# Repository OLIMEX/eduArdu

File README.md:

# eduArdu
Open Source Hardware Educational board based on Arduino Leonardo

Product page: https://www.olimex.com/Products/Duino/AVR/eduArdu/open-source-hardware

Introduction video: https://youtu.be/3kFrveMF56s

# Getting started

## Arduino IDE

* [Download and install Arduino IDE](https://www.arduino.cc/en/Main/Software)
* Open Arduino IDE
* Click **Sketch > Include Library > Add .ZIP library...** and add all libraries provided with this repository
* If you get "arduino Error: 13 INTERNAL: Library install failed: archive is not valid: multiple files found in zip file top level" (usually when you use newer version of Arduino IDE) extract the .zip files into respective folders: `Olimex_Buzzer.zip` into `Olimex_Buzzer` in the same `libraries` folder. Then open Arduino IDE and click `File->Preferences` and change Sketchbook location to the `SOFTWARE` folder of the repo location.
* Open a sketch, compile and upload it to Olimex eduArdu

## Licensee
* Hardware is released under Apache 2.0 Licensee
* Software is released under GPL3 Licensee
* Documentation is released under CC BY-SA 3.0

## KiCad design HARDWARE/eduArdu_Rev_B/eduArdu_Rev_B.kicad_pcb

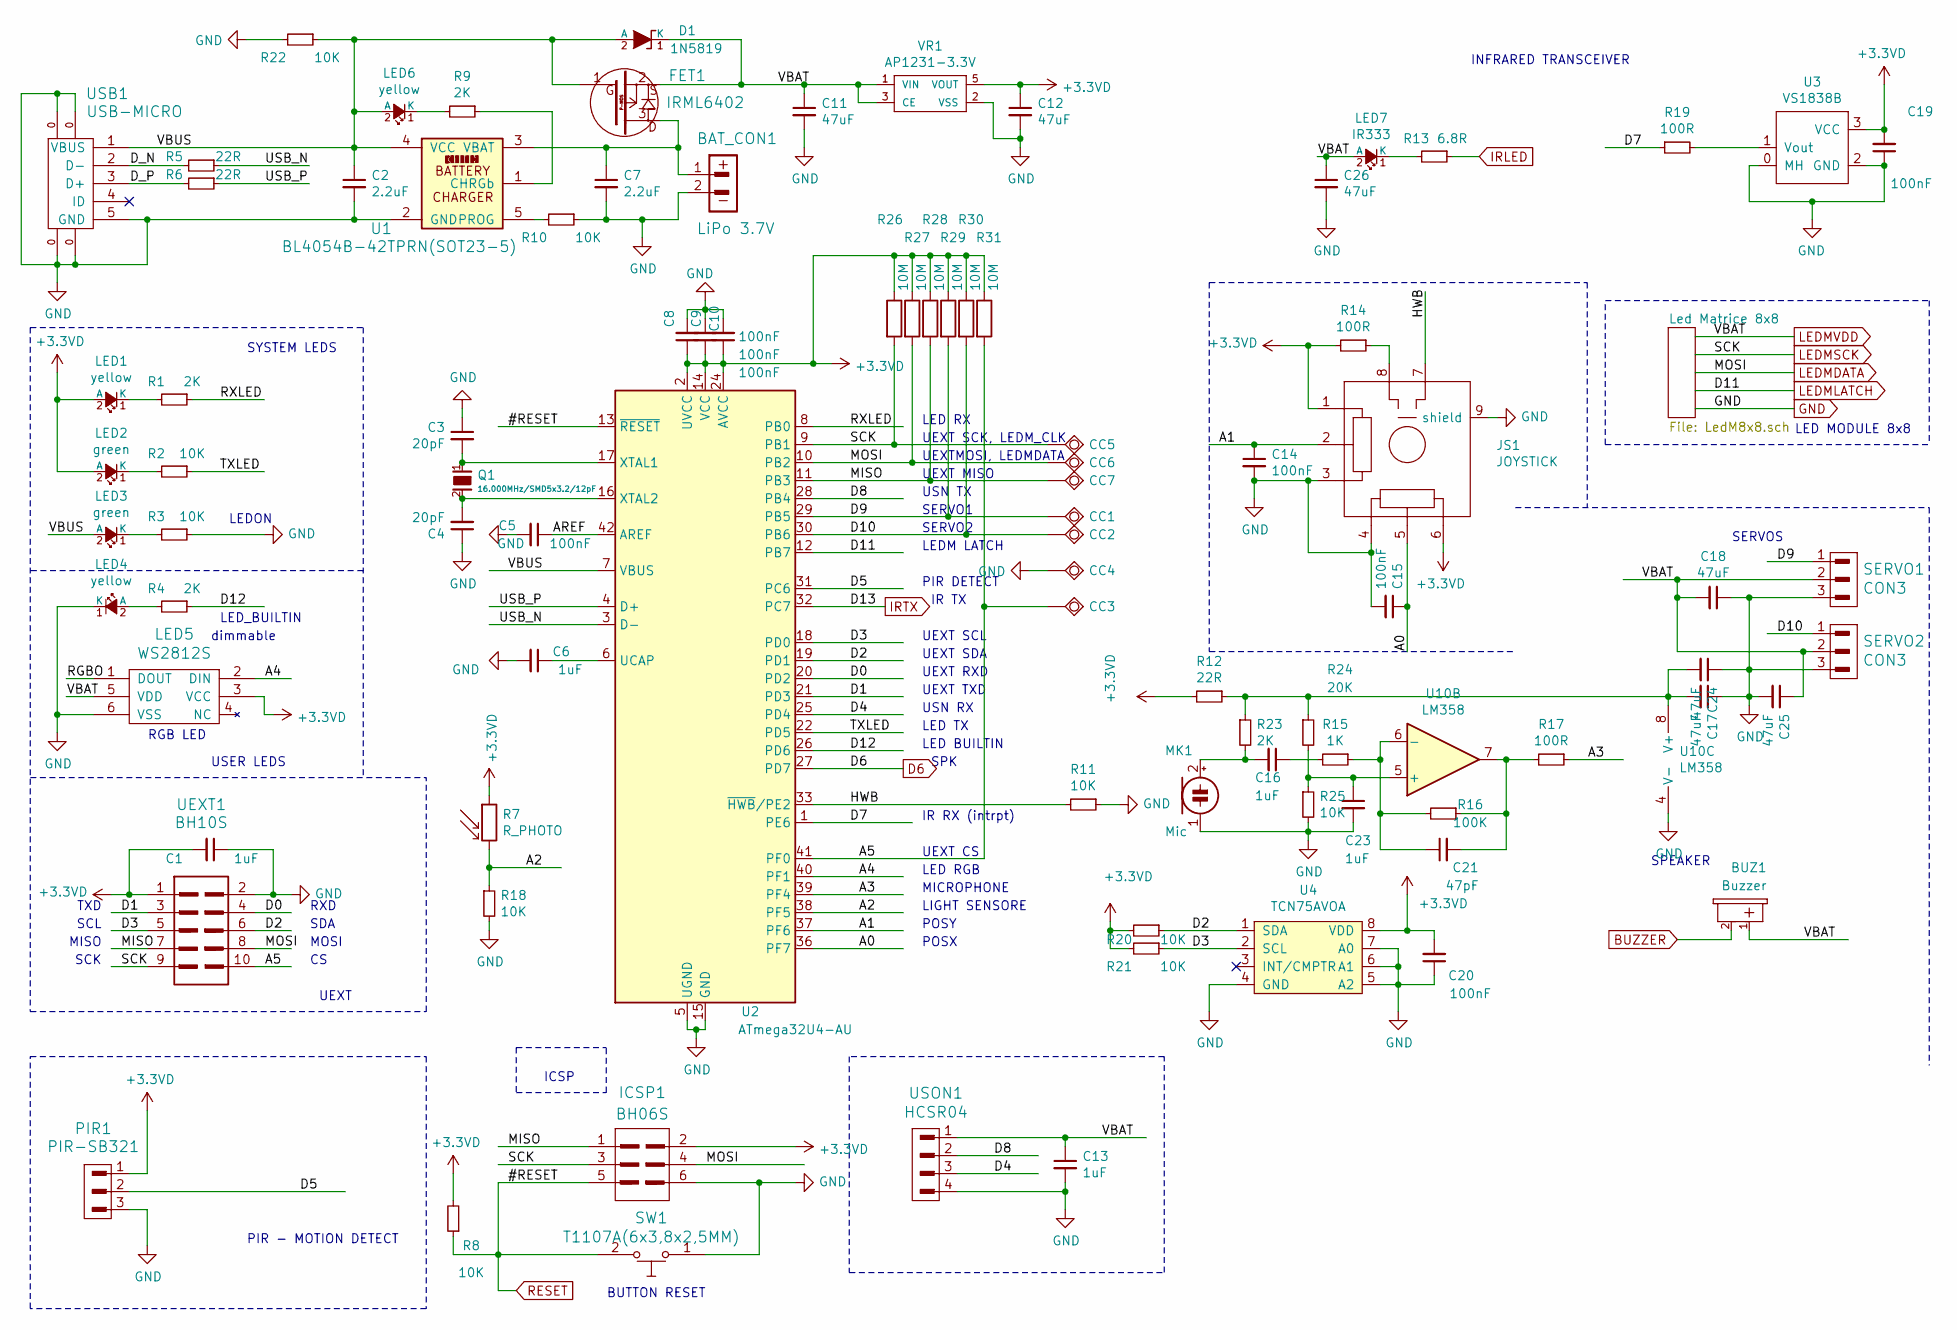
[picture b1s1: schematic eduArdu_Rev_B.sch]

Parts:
BAT_CON1: LiPo 3.7V; LIPO_BAT-CON2DW02R
BUZ1: Buzzer; BUZZER-PB1240
C1, C6, C13, C16, C23: 1uF; C_0603_5MIL_DWS
C2, C7: 2.2uF; C_0603_5MIL_DWS
C3, C4: 20pF; C_0402_5MIL_DWS
C5, C8, C9, C10, C14, C15, C19, C20: 100nF; C_0402_5MIL_DWS
C11, C12, C18, C26: 47uF; C_0805_5MIL_DWS
C17, C24, C25: 47uF; C_0603_5MIL_DWS
C21: 47pF; C_0402_5MIL_DWS
CC1, CC2, CC3, CC4, CC5, CC6, CC7: TESTPAD; Mounting_hole_Shield_4.3mm
D1: 1N5819; SMA-KA
FET1: IRML6402; SOT23
ICSP1: BH06S; HN2x3
JS1: JOYSTICK
LED1, LED4, LED6: yellow; LED_0603_KA
LED2, LED3: green; LED_0603_KA
LED5: WS2812S; WS2812_NO_SILK
LED7: IR333; LED-5mm-PTH-AK
MK1: Mic; MIC
PIR1: PIR-SB321; HN1x3
Q1: 16.000MHz/SMD5x3.2/12pF; HCX-4S_2Pins_5.0x3.2mm
R1, R4, R9, R23: 2K; R_0402_5MIL_DWS
R2, R3, R8, R10, R11, R18, R20, R21, R22, R25: 10K; R_0402_5MIL_DWS
R5, R6, R12: 22R; R_0402_5MIL_DWS
R7: R_PHOTO
R13: 6.8R; R_1206_5MIL_DWS
R14, R17, R19: 100R; R_0402_5MIL_DWS
R15: 1K; R_0402_5MIL_DWS
R16: 100K; R_0402_5MIL_DWS
R24: 20K; R_0402_5MIL_DWS
R26, R27, R28, R29, R30, R31: 10M; R_0402_5MIL_DWS
SERVO1, SERVO2: CON3; HN1x3
SW1: T1107A(6x3,8x2,5MM)
U1: BL4054B-42TPRN(SOT23-5); SOT-23-5
U2: ATmega32U4-AU; TQFP44
U3: VS1838B; RPM7236-H8-V
U4: TCN75AVOA; SO-8
U10: LM358; SO-8
UEXT1: BH10S; UEXTM-SMD
USB1: USB-MICRO; MICRO_USB_5P-F_TYPE_DIP
USON1: HCSR04; USONIC-PING
VR1: AP1231-3.3V; SOT-23-5

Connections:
+3.3VD: C1.2, C8.1, C9.1, C10.1, C12.1, C19.2, C20.2, ICSP1.2, JS1.1, JS1.6, LED1.2 (A), LED2.2 (A), LED5.3 (VCC), PIR1.1, R7.1, R8.2, R12.2, R14.2, R20.2, R21.2, R26.1, R27.1, R28.1, R29.1, R30.1, R31.1, U2.2 (UVCC), U2.14 (VCC), U2.24 (AVCC), U2.34 (VCC), U2.44 (AVCC), U3.3 (VCC), U4.8 (VDD), UEXT1.1, VR1.5 (VOUT)
/A0: C15.1, JS1.5, U2.36 (PF7)
/A1: C14.1, JS1.2, U2.37 (PF6)
/A2: R7.2, R18.1, U2.38 (PF5)
/A3: R17.1, U2.39 (PF4)
/A4: LED5.2 (DIN), U2.40 (PF1)
/A5: CC3.1, R31.2, U2.41 (PF0), UEXT1.10
/AREF: C5.1, U2.42 (AREF)
/D0: U2.20 (PD2), UEXT1.4
/D1: U2.21 (PD3), UEXT1.3
/D2: R20.1, U2.19 (PD1), U4.1 (SDA), UEXT1.6
/D3: R21.1, U2.18 (PD0), U4.2 (SCL), UEXT1.5
/D4: U2.25 (PD4), USON1.3
/D5: PIR1.2, U2.31 (PC6)
/D7: R19.1, U2.1 (PE6)
/D8: U2.28 (PB4), USON1.2
/D9: CC1.1, R29.2, SERVO1.1, U2.29 (PB5)
/D10: CC2.1, R30.2, SERVO2.1, U2.30 (PB6)
/D12: R4.1, U2.26 (PD6)
/D_N: R5.2, USB1.2 (D-)
/D_P: R6.2, USB1.3 (D+)
/HWB: JS1.7, R11.2, U2.33 (~HWB~/PE2)
/MISO: CC7.1, ICSP1.1, R28.2, U2.11 (PB3), UEXT1.7
/RGBO: LED5.1 (DOUT)
/RXLED: R1.1, U2.8 (PB0)
/TXLED: R2.1, U2.22 (PD5)
/USB_N: R5.1, U2.3 (D-)
/USB_P: R6.1, U2.4 (D+)
/VBUS: C2.1, D1.2 (A), FET1.1, LED3.2 (A), LED6.2 (A), R22.1, U1.4 (VCC), U2.7 (VBUS), USB1.1 (VBUS)
BUZZER: BUZ1.2 (MINUS); also elsewhere on the board
D6: U2.27 (PD7); also elsewhere on the board
GND: BAT_CON1.2, C1.1, C2.2, C3.1, C4.1, C5.2, C6.2, C7.2, C8.2, C9.2, C10.2, C11.2, C12.2, C13.2, C14.2, C15.2, C17.1, C18.1, C19.1, C20.1, C23.2, C24.1, C25.2, C26.2, CC4.1, ICSP1.6, JS1.3, JS1.4, JS1.9 (shield), LED4.1 (K), LED5.6 (VSS), MK1.1 (-), PIR1.3, R3.1, R10.1, R11.1, R18.2, R22.2, R25.2, SERVO1.3, SERVO2.3, SW1.1, U1.2 (GND), U2.5 (UGND), U2.15 (GND), U2.23 (GND), U2.35 (GND), U2.43 (GND), U3.0 (MH), U3.2 (GND), U4.4 (GND), U4.5 (A2), U4.6 (A1), U4.7 (A0), U10.4 (V-), UEXT1.2, USB1.0, USB1.5 (GND), USON1.4, VR1.2 (VSS); also elsewhere on the board
IRLED: R13.1; also elsewhere on the board
IRTX: U2.32 (PC7); also elsewhere on the board
LEDMDATA: CC6.1, ICSP1.4, R27.2, U2.10 (PB2), UEXT1.8; also elsewhere on the board
LEDMLATCH: U2.12 (PB7); also elsewhere on the board
LEDMSCK: CC5.1, ICSP1.3, R26.2, U2.9 (PB1), UEXT1.9; also elsewhere on the board
LEDMVDD: BUZ1.1 (PLUS), C11.1, C13.1, C18.2, C25.1, C26.1, D1.1 (K), FET1.2, LED5.5 (VDD), LED7.2 (A), SERVO1.2, SERVO2.2, USON1.1, VR1.1 (VIN), VR1.3 (CE); also elsewhere on the board
unnamed: BAT_CON1.1, C7.1, FET1.3, U1.3 (VBAT)
unnamed: C3.2, Q1.1, U2.17 (XTAL1)
unnamed: C4.2, Q1.2, U2.16 (XTAL2)
unnamed: C6.1, U2.6 (UCAP)
unnamed: C16.1, R15.2
unnamed: C16.2, MK1.2 (+), R23.2
unnamed: C17.2, C24.2, R12.1, R23.1, R24.1, U10.8 (V+)
unnamed: C21.1, R15.1, R16.2, U10.6 (-)
unnamed: C21.2, R16.1, R17.2, U10.7
unnamed: C23.1, R24.2, R25.1, U10.5 (+)
unnamed: JS1.8, R14.1
unnamed: LED1.1 (K), R1.2
unnamed: LED2.1 (K), R2.2
unnamed: LED3.1 (K), R3.2
unnamed: LED4.2 (A), R4.2
unnamed: LED6.1 (K), R9.2
unnamed: LED7.1 (K), R13.2
unnamed: R9.1, U1.1 (CHRGb)
unnamed: R10.2, U1.5 (PROG)
unnamed: R19.2, U3.1 (Vout)
RESET: ICSP1.5, R8.1, SW1.2, U2.13 (~RESET); also elsewhere on the board

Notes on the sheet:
RXD
SDA
MOSI
TXD
SCL
MISO
SCK
LED_BUILTIN
RGB LED
dimmable
LEDON
PIR DETECT
LED TX
LED RX
LED BUILTIN
ICSP
LED RGB
POSX
POSY
BUTTON RESET
USN RX
USN TX
INFRARED TRANSCEIVER
UEXT SCL
UEXT SDA
UEXT CS
UEXT TXD
UEXT RXD
SERVO1
SERVO2
SPK
UEXT SCK, LEDM_CLK
UEXTMOSI, LEDMDATA
UEXT MISO
LEDM LATCH
LED MODULE 8x8
IR RX (intrpt)
SERVOS
SPEAKER
UEXT

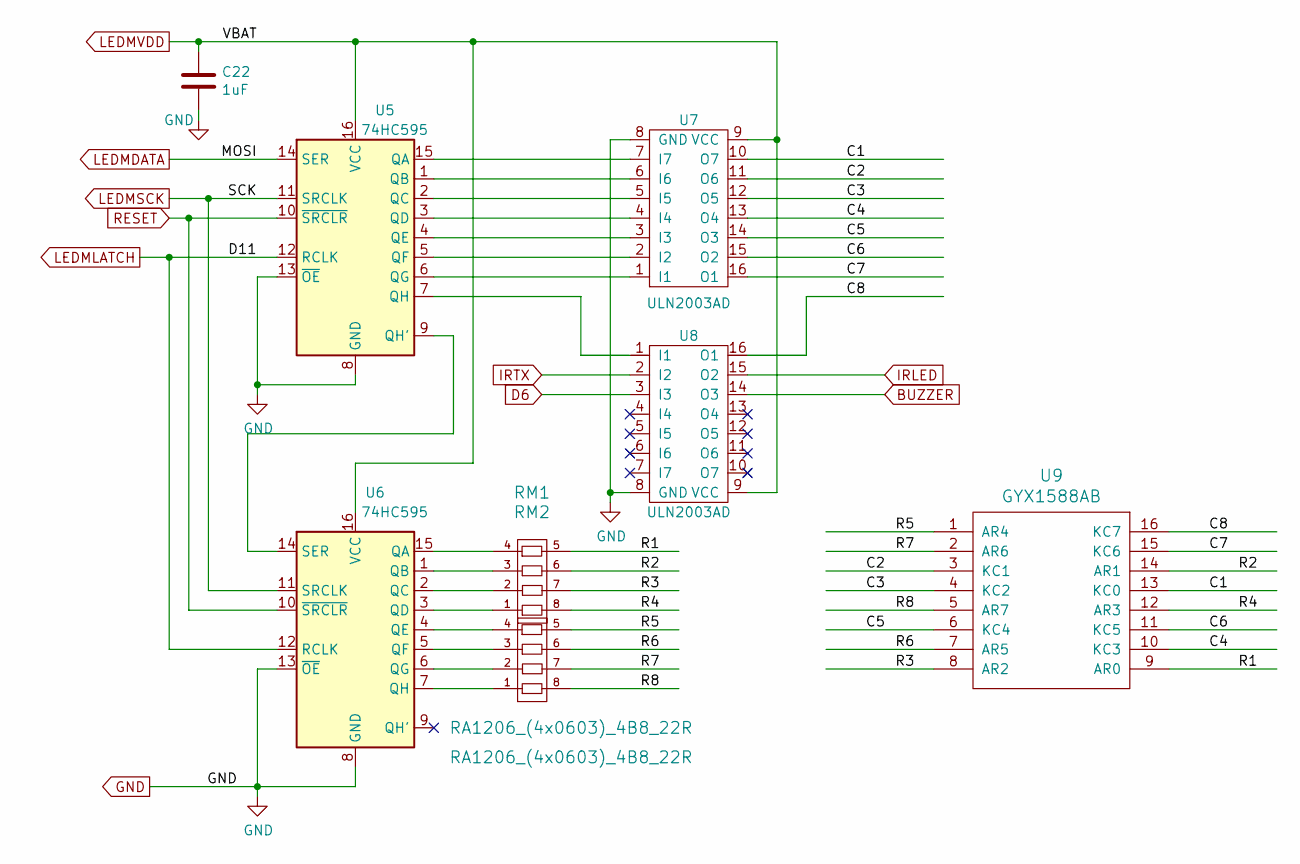
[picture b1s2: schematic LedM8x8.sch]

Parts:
C22: 1uF; C_0603_5MIL_DWS
RM1, RM2: RA1206_(4x0603)_4B8_22R; RA1206_(4X0603)_4B8_mine
U5, U6: 74HC595; SO-16
U7, U8: ULN2003AD; SO-16
U9: GYX1588AB

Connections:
/Led Matrice 8x8/C1: U7.10 (O7), U9.13 (KC0)
/Led Matrice 8x8/C2: U7.11 (O6), U9.3 (KC1)
/Led Matrice 8x8/C3: U7.12 (O5), U9.4 (KC2)
/Led Matrice 8x8/C4: U7.13 (O4), U9.10 (KC3)
/Led Matrice 8x8/C5: U7.14 (O3), U9.6 (KC4)
/Led Matrice 8x8/C6: U7.15 (O2), U9.11 (KC5)
/Led Matrice 8x8/C7: U7.16 (O1), U9.15 (KC6)
/Led Matrice 8x8/C8: U8.16 (O1), U9.16 (KC7)
/Led Matrice 8x8/R1: RM1.5, U9.9 (AR0)
/Led Matrice 8x8/R2: RM1.6, U9.14 (AR1)
/Led Matrice 8x8/R3: RM1.7, U9.8 (AR2)
/Led Matrice 8x8/R4: RM1.8, U9.12 (AR3)
/Led Matrice 8x8/R5: RM2.5, U9.1 (AR4)
/Led Matrice 8x8/R6: RM2.6, U9.7 (AR5)
/Led Matrice 8x8/R7: RM2.7, U9.2 (AR6)
/Led Matrice 8x8/R8: RM2.8, U9.5 (AR7)
BUZZER: U8.14 (O3); also elsewhere on the board
D6: U8.3 (I3); also elsewhere on the board
GND: C22.2, U5.8 (GND), U5.13 (~OE), U6.8 (GND), U6.13 (~OE), U7.8 (GND), U8.8 (GND); also elsewhere on the board
IRLED: U8.15 (O2); also elsewhere on the board
IRTX: U8.2 (I2); also elsewhere on the board
LEDMDATA: U5.14 (SER); also elsewhere on the board
LEDMLATCH: U5.12 (RCLK), U6.12 (RCLK); also elsewhere on the board
LEDMSCK: U5.11 (SRCLK), U6.11 (SRCLK); also elsewhere on the board
LEDMVDD: C22.1, U5.16 (VCC), U6.16 (VCC), U7.9 (VCC), U8.9 (VCC); also elsewhere on the board
unnamed: RM1.1, U6.3 (QD)
unnamed: RM1.2, U6.2 (QC)
unnamed: RM1.3, U6.1 (QB)
unnamed: RM1.4, U6.15 (QA)
unnamed: RM2.1, U6.7 (QH)
unnamed: RM2.2, U6.6 (QG)
unnamed: RM2.3, U6.5 (QF)
unnamed: RM2.4, U6.4 (QE)
unnamed: U5.1 (QB), U7.6 (I6)
unnamed: U5.2 (QC), U7.5 (I5)
unnamed: U5.3 (QD), U7.4 (I4)
unnamed: U5.4 (QE), U7.3 (I3)
unnamed: U5.5 (QF), U7.2 (I2)
unnamed: U5.6 (QG), U7.1 (I1)
unnamed: U5.7 (QH), U8.1 (I1)
unnamed: U5.9 (QH'), U6.14 (SER)
unnamed: U5.15 (QA), U7.7 (I7)
RESET: U5.10 (~SRCLR), U6.10 (~SRCLR); also elsewhere on the board

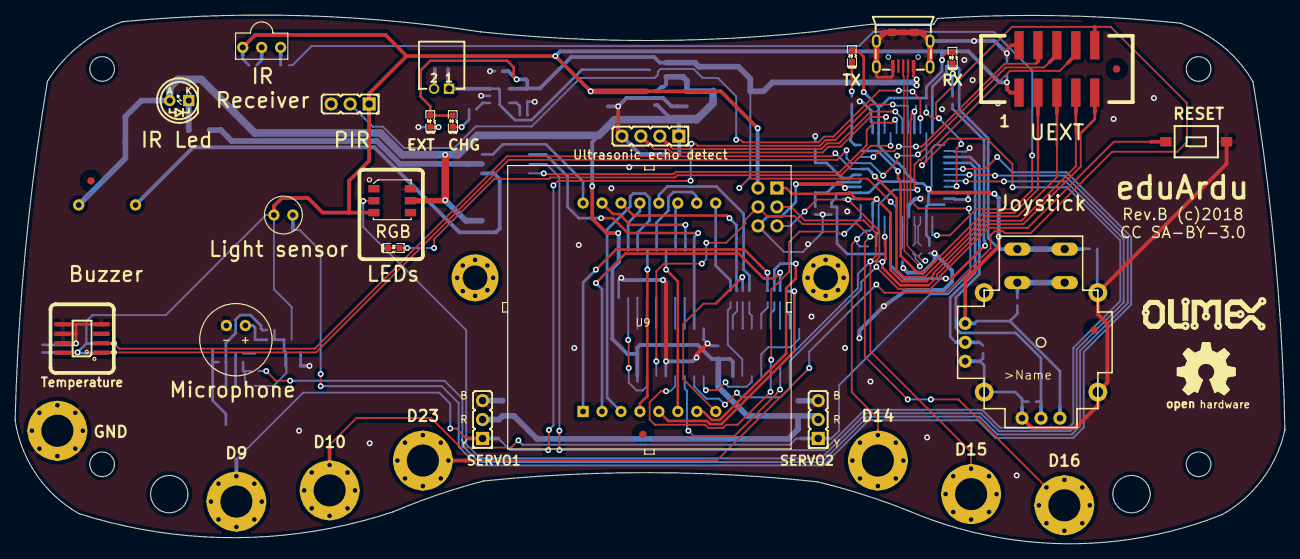
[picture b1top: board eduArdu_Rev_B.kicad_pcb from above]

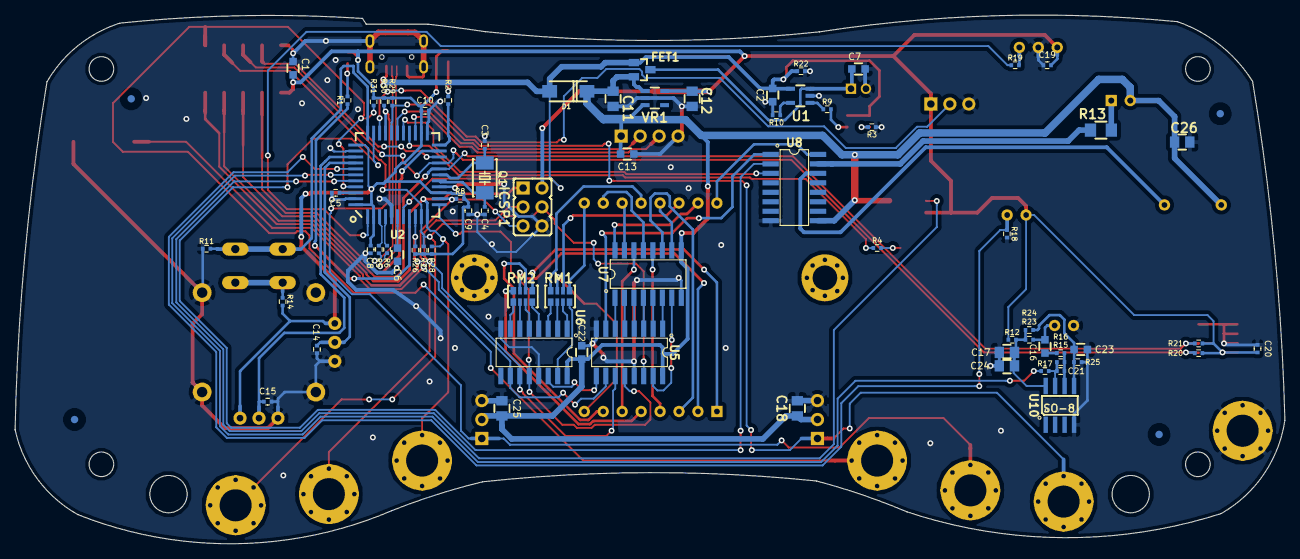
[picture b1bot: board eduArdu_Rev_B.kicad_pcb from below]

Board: 2 copper layers, 170.2 x 70.9 mm, 115 parts (74 on the bottom side), 91 nets.

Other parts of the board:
MountingHole: NPTH_2.7mm
MountingHole#2, MountingHole#3, MountingHole#4, MountingHole#5, MountingHole#6: NPTH_2.7mm
MountingHoleShield**: Mounting_hole_Shield_3.3mm
MountingHoleShield**#2: Mounting_hole_Shield_3.3mm
Ref*: Val**; Fiducial1x3_transp
Ref*#2, Ref*#3, Ref*#4, Ref*#5, Ref*#6, Ref*#7, Ref*#8: Val**; Fiducial1x3_transp

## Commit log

2018-12-07 Initial upload of PCB CAD files, Arduino examples and how to configure Snap4Arduino to work with eduArdu
2018-12-10 label D13 changed to D23
2018-12-12 libraries update
2018-12-12 more updates on software
2018-12-13 software libraries update
2018-12-17 fix firmata size
2018-12-20 eduAedu and Snap tutorial and examples
2018-12-23 README.md: Add getting started notes
    Add the exact steps to get stareted with the provided examples
    in Arduino IDE by importing the libraries, compiling and
    uploading the sketches to Olimex eduArdu.
2019-04-04 15_eduArdu_IR_LED.ino: Change LED on IR signal
    The code controls the LED changing its color depending on the infrared signal sent to it.
    Tested with Samsung remote controller. Currently supports 2 colours corresponding to two IR signals.
2019-05-15 add English document for SNAP
2019-07-16 Capacitive Buttons, Robot, LED Matrix, Arduino install
2019-07-16 fix duplicate numbers
2019-07-29 add Scratch3 tutorial and demo
2020-02-23 clean code
2020-04-08 updated libraries add 21 22 demo code, upload challenges
2020-04-11 23_eduArdu_Joystick.ino: Joystick as arrow keys
    Example implementation that emulates keyboard arrow keys when the
    joystick is pressed in the appropaite direction. Useful for using
    eduArdu as a super simple USB HID gamepad for games like 2048.
2020-04-12 modemmanager fix reported by Leon Anavi

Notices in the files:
HARDWARE/eduArdu_Rev_B/eduArdu_Rev_B.kicad_pcb:
Rev.B (c)2018
